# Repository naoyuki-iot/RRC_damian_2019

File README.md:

# RRC_damian_2019
- "Damian" is a rescue dummy as a rescuer on RRC.

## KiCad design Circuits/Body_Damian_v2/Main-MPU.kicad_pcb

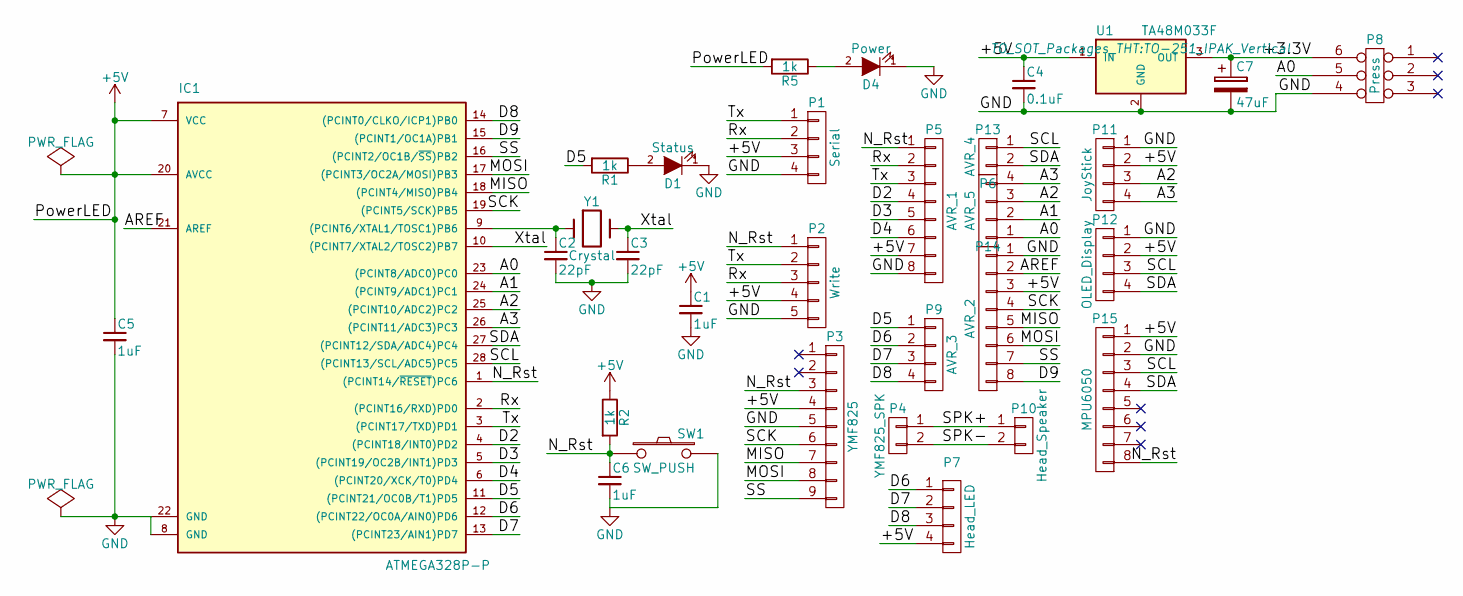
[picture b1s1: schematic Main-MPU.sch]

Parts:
C1, C5, C6: 1uF; C_Disc_D3.0mm_W1.6mm_P2.50mm
C2, C3: 22pF; C_Disc_D3.0mm_W1.6mm_P2.50mm
C4: 0.1uF; C_Disc_D3.0mm_W1.6mm_P2.50mm
C7: 47uF; CP_Radial_D5.0mm_P2.00mm
D1: Status; LED_D5.0mm
D4: Power; LED_D5.0mm
IC1: ATMEGA328P-P; DIP-28_W7.62mm_LongPads
P1: Serial; JST_PH_B4B-PH-K_04x2.00mm_Straight
P2: Write; Pin_Header_Straight_1x05_Pitch2.54mm
P3: YMF825; Socket_Strip_Straight_1x09_Pitch2.54mm
P4: YMF825_SPK; Socket_Strip_Straight_1x02_Pitch2.54mm
P5: AVR_1; Pin_Header_Straight_1x08_Pitch2.54mm
P6: AVR_2; Pin_Header_Straight_1x08_Pitch2.54mm
P7: Head_LED; JST_PH_S4B-PH-K_04x2.00mm_Angled
P8: Press; DIP-6_W10.16mm
P9: AVR_3; Pin_Header_Straight_1x04_Pitch2.54mm
P10: Head_Speaker; JST_PH_S3B-PH-K_03x2.00mm_Angled
P11: JoyStick; JST_PH_B4B-PH-K_04x2.00mm_Straight
P12: OLED_Display; Socket_Strip_Straight_1x04_Pitch2.54mm
P13: AVR_4; Pin_Header_Straight_1x02_Pitch2.54mm
P14: AVR_5; Pin_Header_Straight_1x04_Pitch2.54mm
P15: MPU6050; Socket_Strip_Straight_1x08_Pitch2.54mm
R1, R2, R5: 1k; R_Axial_DIN0207_L6.3mm_D2.5mm_P7.62mm_Horizontal
SW1: SW_PUSH; SW_PUSH_6mm_h7.3mm
U1: TA48M033F; TO-251_IPAK_Vertical
Y1: Crystal; Crystal_HC49-4H_Vertical

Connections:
+5V: C1.1, C4.1, C5.1, IC1.7 (VCC), IC1.20 (AVCC), P1.3, P2.4, P3.4, P5.7, P6.3, P7.4, P11.2, P12.2, P15.1, R2.1, R5.2, U1.1 (IN)
/+3.3V: C7.1, P8.6, U1.3 (OUT)
/A0: IC1.23 ((PCINT8/ADC0)PC0), P8.5, P14.1
/A1: IC1.24 ((PCINT9/ADC1)PC1), P14.2
/A2: IC1.25 ((PCINT10/ADC2)PC2), P11.3, P14.3
/A3: IC1.26 ((PCINT11/ADC3)PC3), P11.4, P14.4
/AREF: IC1.21 (AREF), P6.2
/D2: IC1.4 ((PCINT18/INT0)PD2), P5.4
/D3: IC1.5 ((PCINT19/OC2B/INT1)PD3), P5.5
/D4: IC1.6 ((PCINT20/XCK/T0)PD4), P5.6
/D5: IC1.11 ((PCINT21/OC0B/T1)PD5), P9.1, R1.2
/D6: IC1.12 ((PCINT22/OC0A/AIN0)PD6), P7.1, P9.2
/D7: IC1.13 ((PCINT23/AIN1)PD7), P7.2, P9.3
/D8: IC1.14 ((PCINT0/CLKO/ICP1)PB0), P7.3, P9.4
/D9: IC1.15 ((PCINT1/OC1A)PB1), P6.8
/MISO: IC1.18 ((PCINT4/MISO)PB4), P3.7, P6.5
/MOSI: IC1.17 ((PCINT3/OC2A/MOSI)PB3), P3.8, P6.6
/N_Rst: C6.1, IC1.1 ((PCINT14/~RESET~)PC6), P2.1, P3.3, P5.1, P15.8, R2.2, SW1.1
/Rx: IC1.2 ((PCINT16/RXD)PD0), P1.2, P2.3, P5.2
/SCK: IC1.19 ((PCINT5/SCK)PB5), P3.6, P6.4
/SCL: IC1.28 ((PCINT13/SCL/ADC5)PC5), P12.3, P13.1, P15.3
/SDA: IC1.27 ((PCINT12/SDA/ADC4)PC4), P12.4, P13.2, P15.4
/SPK+: P4.1, P10.1
/SPK-: P4.2, P10.2
/SS: IC1.16 ((PCINT2/OC1B/~SS~)PB2), P3.9, P6.7
/Tx: IC1.3 ((PCINT17/TXD)PD1), P1.1, P2.2, P5.3
/Xtal: C3.1, IC1.10 ((PCINT7/XTAL2/TOSC2)PB7), Y1.2
GND: C1.2, C2.2, C3.2, C4.2, C5.2, C6.2, C7.2, D1.1 (K), D4.1 (K), IC1.8 (GND), IC1.22 (GND), P1.4, P2.5, P3.5, P5.8, P6.1, P8.4, P11.1, P12.1, P15.2, SW1.2, U1.2 (GND)
unnamed: C2.1, IC1.9 ((PCINT6/XTAL1/TOSC1)PB6), Y1.1
unnamed: D1.2 (A), R1.1
unnamed: D4.2 (A), R5.1

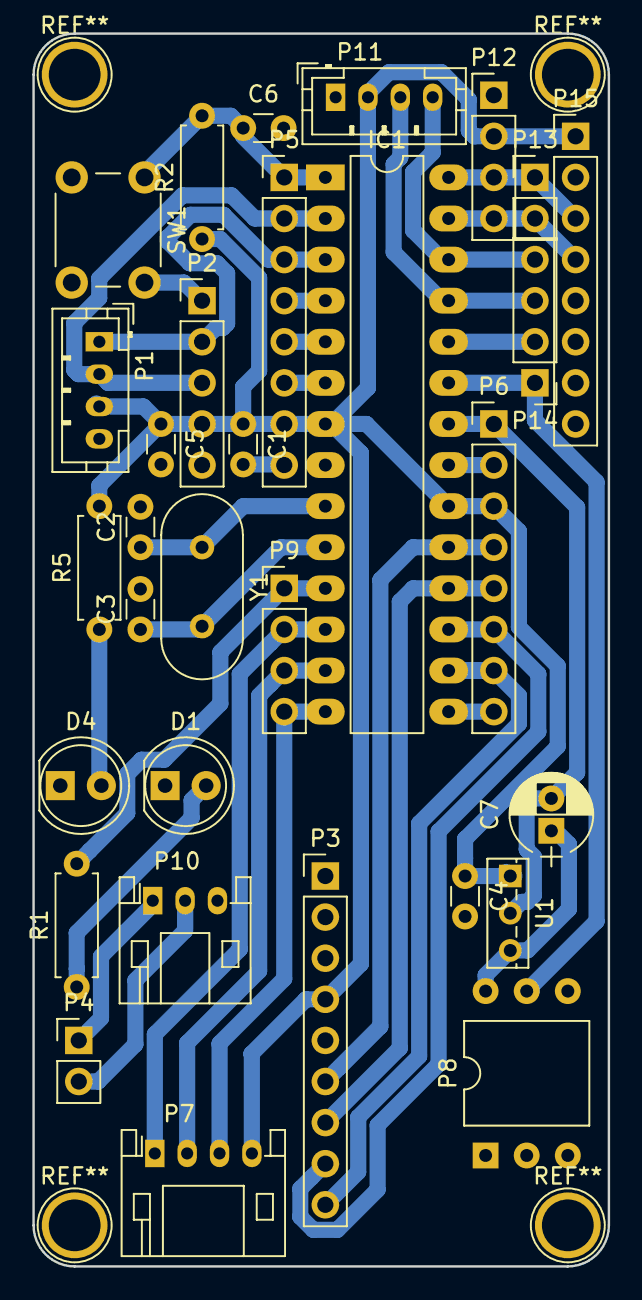
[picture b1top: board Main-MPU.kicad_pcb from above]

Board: 2 copper layers, 35.6 x 76.2 mm, 31 parts (0 on the bottom side), 31 nets.

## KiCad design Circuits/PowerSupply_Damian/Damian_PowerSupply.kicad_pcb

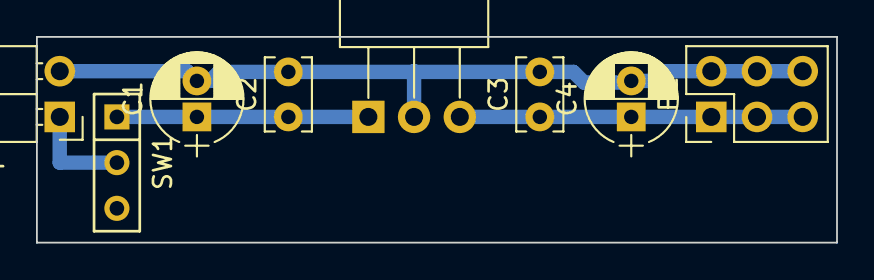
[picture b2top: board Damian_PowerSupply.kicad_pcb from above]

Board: 2 copper layers, 44.4 x 11.4 mm, 8 parts (0 on the bottom side), 4 nets.

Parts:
BT1: Battery; Pin_Header_Angled_1x02_Pitch2.54mm
C1, C4: CP; CP_Radial_D5.0mm_P2.00mm
C2, C3: C; C_Rect_L4.0mm_W2.5mm_P2.50mm
P1: CONN_02X03; Pin_Header_Straight_2x03_Pitch2.54mm
SW1: SWITCH_INV; SW_Micro_SPST
U1: 7805; TO-126_Horizontal

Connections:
+5V: C3.1, C4.1, P1.1, P1.3, P1.5, U1.3
GND: BT1.2, C1.2, C2.2, C3.2, C4.2, P1.2, P1.4, P1.6, U1.2
unnamed: BT1.1, SW1.2
unnamed: C1.1, C2.1, SW1.1, U1.1

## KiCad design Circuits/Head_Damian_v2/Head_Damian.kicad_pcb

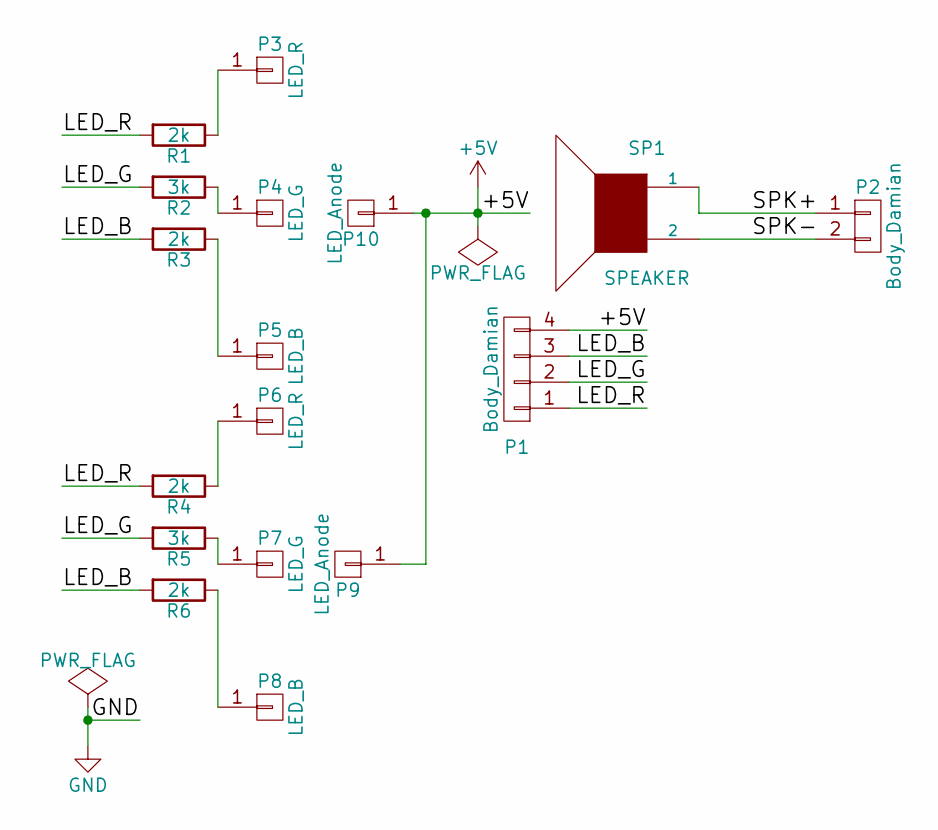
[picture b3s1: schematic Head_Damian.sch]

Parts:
P1: Body_Damian; JST_PH_S4B-PH-K_04x2.00mm_Angled
P2: Body_Damian; JST_PH_S3B-PH-K_03x2.00mm_Angled
P3, P6: LED_R; Socket_Strip_Straight_1x01_Pitch2.54mm
P4, P7: LED_G; Socket_Strip_Straight_1x01_Pitch2.54mm
P5, P8: LED_B; Socket_Strip_Straight_1x01_Pitch2.54mm
P9, P10: LED_Anode; Socket_Strip_Straight_1x01_Pitch2.54mm
R1, R3, R4, R6: 2k; R_Axial_DIN0207_L6.3mm_D2.5mm_P7.62mm_Horizontal
R2, R5: 3k; R_Axial_DIN0207_L6.3mm_D2.5mm_P7.62mm_Horizontal
SP1: SPEAKER; Socket_Strip_Straight_1x02_Pitch2.54mm

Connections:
+5V: P1.4, P9.1, P10.1
/LED_B: P1.3, R3.2, R6.2
/LED_G: P1.2, R2.2, R5.2
/LED_R: P1.1, R1.2, R4.2
/SPK+: P2.1, SP1.1
/SPK-: P2.2, SP1.2
unnamed: P3.1, R1.1
unnamed: P4.1, R2.1
unnamed: P5.1, R3.1
unnamed: P6.1, R4.1
unnamed: P7.1, R5.1
unnamed: P8.1, R6.1

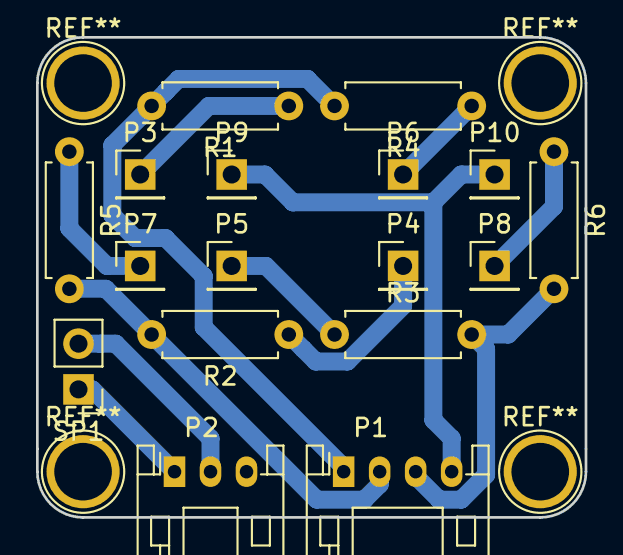
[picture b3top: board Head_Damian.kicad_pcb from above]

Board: 2 copper layers, 30.5 x 26.7 mm, 17 parts (0 on the bottom side), 12 nets.

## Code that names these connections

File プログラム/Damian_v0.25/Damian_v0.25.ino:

#include <Wire.h>
#include <avr/pgmspace.h>   // 配列をフラッシュメモリからロードするためのもの
#include <TimerOne.h> //tone関数とバッティングするのでMstimer2(Timer2)でなくTimer1を使用
#define OLED_ADDR (0x3C) //OLED address 製品に記載の数値は7bitなので、8bitに変換して1bit右へずらした値(78>>3c)

#include <SPI.h>//音源モジュール(YMF825)用
/*音源モジュールの接続
   RST_N- Pin9   
   SS   - Pin10
   MOSI - Pin11
   MISO - Pin12
   SCK  - Pin13
 */
#define OUTPUT_power 0//0 :5V 1:3.3V//音源モジュール動作電圧設定（Arduinoは基本的に5V）

#define BUTTON_CHANGE_COLOR 3 //3番ピンにボタンを押すと目の色が変わるスイッチを接続 
#define BUTTON_CHANGE_HZ 4 //4番ピンにボタンを押すとブザーの周波数が変わるスイッチを接続
#define LED_R 6 //フルカラーLED赤を6番ピンに接続
#define LED_G 7 //フルカラーLED緑を7番ピンに接続
#define LED_B 8 //フルカラーLED青を8番ピンに接続


#define NO_USE_ANALOGPIN1 A1
#define NO_USE_ANALOGPIN4 A4
#define NO_USE_ANALOGPIN5 A5
//未使用のアナログピンを乱数生成に使う

#define BUTTON_ON LOW
#define BUTTON_OFF HIGH

enum {BLACK, RED, GREEN, YELLOW, BLUE, PURPLE, LIGHTBLUE, WHITE}; //RGB順、黒000 赤001 緑010 黄011 青100 紫101 水110 白111(BGR):enumは列挙型変数であり、配列内の先頭の文字から順々に0,1,2...と定める,
const char * const color_led_name[] = {"Black", "Red", "Green", "Yellow", "Blue", "Purple", "Water", "White"}; //表示用(2017)const:定数,char:文字列を入れる型
uint8_t color_led; //顔の色,unit8_t:8bitの非負整数を格納する型(16なら16bit)

const uint16_t  hex[50][3]={
  {0,0,0},
  {196,0x23,0x17},
  {208,0x23,0x37},
  {220,0x23,0x59},
  {233,0x23,0x7D},
  {247,0x2B,0x22},
  {262,0x14,0x65},
  {277,0x14,0x7A},
  {294,0x1C,0x11},
  {311,0x1C,0x29},
  {330,0x1C,0x42},
  {349,0x1C,0x5D},
  {370,0x1C,0x79},
  {392,0x24,0x17},
  {415,0x24,0x37},
  {440,0x24,0x59},
  {466,0x24,0x7D},
  {494,0x2C,0x22},
  {523,0x15,0x65},
  {554,0x15,0x7A},
  {587,0x1D,0x11},
  {622,0x1D,0x29},
  {659,0x1D,0x42},
  {699,0x1D,0x5D},
  {740,0x1D,0x79},
  {784,0x25,0x17},
  {831,0x25,0x37},
  {880,0x25,0x59},
  {932,0x25,0x7D},
  {987,0x2D,0x22},
  {1047,0x16,0x65},
  {1109,0x16,0x7A},
  {1175,0x1E,0x11},
  {1244,0x1E,0x29},
  {1318,0x1E,0x42},
  {1397,0x1E,0x5D},
  {1480,0x1E,0x79},
  {1568,0x26,0x17},
  {1661,0x26,0x37},
  {1760,0x26,0x59},
  {1865,0x26,0x7D},
  {1976,0x2E,0x22},
  {2093,0x17,0x65},
  {2218,0x17,0x7A},
  {2349,0x1F,0x11},
  {2489,0x1F,0x29},
  {2637,0x1F,0x42},
  {2794,0x1F,0x5D},
  {2960,0x1F,0x79},
  {3136,0x27,0x17}
  };//音源周波数パラメータ：{周波数,パラメータ1,パラメータ2}の順
  
const uint16_t buzzer_Hz_pattern[]={
      hex[0][0],hex[1][0],hex[2][0],hex[3][0],hex[4][0],hex[5][0],hex[6][0],hex[7][0],hex[8][0],hex[9][0],hex[10][0],
      hex[11][0],hex[12][0],hex[13][0],hex[14][0],hex[15][0],hex[16][0],hex[17][0],hex[18][0],hex[19][0],hex[20][0],
      hex[21][0],hex[22][0],hex[23][0],hex[24][0],hex[25][0],hex[26][0],hex[27][0],hex[28][0],hex[29][0],hex[30][0],
      hex[31][0],hex[32][0],hex[33][0],hex[34][0],hex[35][0],hex[36][0],hex[37][0],hex[38][0],hex[39][0],hex[40][0],
      hex[41][0],hex[42][0],hex[43][0],hex[44][0],hex[45][0],hex[46][0],hex[47][0],hex[48][0],hex[49][0],hex[50][0]
      };//ブザーの周波数パターン生成のために多次元配列の1列目の要素を取り出す
      
const uint8_t buzzer_Hz_num = sizeof(buzzer_Hz_pattern) / sizeof(buzzer_Hz_pattern[0]); //ブザー周波数のパターンの数
uint8_t randomnumber_Hz;//Generateにあるローカル変数をグローバル変数にした
uint16_t buzzer_Hz = hex[1][0]; //ブザーの周波数(2018)
uint8_t buzzer_pattern[12] = {0, 0, 0, 1, 1, 1, 1, 1, 1, 1, 1, 1}; //ブザーパターン、000はスタートビット
//uint8_t buzzer_pattern[12] = {1, 1, 1, 1, 1, 1, 1, 1, 1, 1, 1, 1}; //ブザーパターン、000はスタートビット(テスト用)
//uint8_t buzzer_pattern[12] = {0, 1, 0, 1, 0, 1, 0, 1, 0, 1, 0, 1}; //ブザーパターン、000はスタートビット(テスト用)

const uint8_t pattern_num = sizeof(buzzer_pattern); //ブザーのビット数:sizeof(x)は変数xのメモリサイズを調べるもの
void setup() {
  Serial.begin(115200);//シリアル通信開始
  
  SPI.setBitOrder(MSBFIRST);//SPIのビット設定:MSBFIRST(most-significant bit first)
  SPI.setClockDivider(SPI_CLOCK_DIV8);//SPIクロック設定(分周値=8)
  SPI.setDataMode(SPI_MODE0);//SPI転送モード設定
  SPI.begin();//音源モジュールの通信開始
  
  Wire.begin();//I2C通信の開始
  setup_i2c();//I2C接続のOLED液晶に状態表示を行う関数："i2C_OLED_Func"タブ参照
  Display_Black();//上記のOLED液晶の初期化用関数："i2C_OLED_Func"タブ参照

  randomSeed(analogRead(NO_USE_ANALOGPIN1)); //未接続のアナログピンを用いて毎回乱数列を変化させる（ブザー周波数のパターンが多いため使うアナログピンを1つ→4つに）
  randomSeed(analogRead(NO_USE_ANALOGPIN4));
  randomSeed(analogRead(NO_USE_ANALOGPIN5));
  
  pinMode(LED_R, OUTPUT);
  pinMode(LED_G, OUTPUT);
  pinMode(LED_B, OUTPUT);//LED3つ出力設定
  pinMode(BUTTON_CHANGE_COLOR, INPUT_PULLUP);
  pinMode(BUTTON_CHANGE_HZ, INPUT_PULLUP); //LEDと周波数を変えるスイッチ2つをプルアップ接続

  pinMode(9,OUTPUT);
  pinMode(10,OUTPUT);
  set_ss_pin(HIGH);//音源モジュール設定
  
  color_led = GenerateLedColor(); //LEDの色を生成
  buzzer_Hz = GenerateBuzzerHz(); //ブザー周波数を生成
  GenerateBuzzerPattern(); //ブザーパターンを生成
  CheckSerialMonitor(); //シリアルモニターに値を表示する
  Timer1.initialize(500000UL); //500ms(500000us)ごとに呼び出す
  Timer1.attachInterrupt(BeepBuzzer); //割込みで呼び出す関数
  
  init_825();
  set_tone();
  set_ch();  //"YMF825_Func"参照
}

void loop() {
  FlushLed(); //LEDを光らせる
  DisplayState(); //I2C接続のOLED液晶に現在の状態を表示する
  ChangePattern(); //LED,ブザーのパターンを変更する
  NeckPositionState();//首(=ジョイスティックモジュール)の傾きの状態をシリアルモニタに表示する
}

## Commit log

2020-03-20 Add files via upload
    Arduino
2020-03-20 Arduino
2020-03-20 Add files via upload
    Using KiCAD
2020-03-20 Media
2020-06-12 Create fp-info-cache
